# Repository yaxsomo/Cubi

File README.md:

### Description
Simple open source bluetooth controlled wheeled robot. Mechanical design, electronics and software designs available on this repo.
I used @Gregwar's Holo as a starting point.

The initial design is a cube like robot :

https://www.youtube.com/watch?v=2ZDV0_4vD0g

https://www.youtube.com/watch?v=TOusHRbKWQg

A second design was also made to play around cart-poling:

https://www.youtube.com/watch?v=Ubej95gH9Gs

TODO:

- Add Julien's O. designs and events

- Add Julien's A. and Jérémy's designs and event (cap science)

### Simulation
Some simulation stuff (simple kinematic control, inverted pendulum tests) is available in Python here :
https://bitbucket.org/RemiFabre/cubi/src/master/simulation/

0) Installation
You'll need Python (any version should work) and pygame
```
pip install pygame
```

1) Simple control of a wheeled robot (click around)
```
python main.py
```
https://www.youtube.com/watch?v=O8ZoUAvGYmE

2) Inverted pendulum (cart-pole) simulation
```
python cart_pole.py
```
https://www.youtube.com/watch?v=xhEcLnnj7fg

### How to make it work
You'll have to install the arm cross-compilation tools. On debian-like distributions,
you can get it with:

```
    sudo aptitude install build-essential git-core dfu-util openocd python \
        python-serial binutils-arm-none-eabi gcc-arm-none-eabi libstdc++-arm-none-eabi-newlib
```
If you're running an Ubuntu 14.04 or older, you might need to install the libstdc++-arm-none-eabi-newlib packet by hand. Download link :
http://ftp.de.debian.org/debian/pool/main/libs/libstdc++-arm-none-eabi/libstdc++-arm-none-eabi-newlib_4.8.3-9+4_all.deb

Command (if a conflict rises, you can add --force-overwrite to the following line):
```
	sudo dpkg -i libstdc++-arm-none-eabi-newlib_4.8.3-9+4_all.deb
```

Then go to Cubi/firmware/src and run :

```
bash ./prepare.sh
```

Then, go to the `firmware/` directory and edit the `Makefile` to set the appropriate
`BOARD` variable, targetting your servo.

You can then run:

```
make
```

Use an USB cable to connect your pc with the robot's board

```
make install
```
If you didn't follow this section to setup udev rules, you might need to ```sudo make install``` instead

http://static.leaflabs.com/pub/leaflabs/maple-docs/0.0.12/unix-toolchain.html#toolchain-udev

### Bluetooth
You can control the robot without the need of a cable. The most straight-forward way is to download the "Metabot" app from Google Play. Once on the app you can scan for devices, find your robot and pair it with your phone.

If you want to pair your PC with your robot, one method is as follows (Ubuntu).

Uninstall modemmanager (not needed but causes some issues)

```
    sudo apt-get purge modemmanager
```

Scan for bluetooth devices and save the adress (e.g. 98:D3:37:90:ED:D6) of your robot. For example, we use blueman-manager :

```
    sudo apt-get install blueman
    sudo blueman-manager
```

Assign a serial port to the connection. You can do that on the graphical interface of blueman-manager but doing it directly with rfcomm seems more robust :

```
    sudo rfcomm bind /dev/rfcomm0 98:D3:37:90:ED:D6
```

Now you can access the remote terminal on the robot with :

```
    cu -l /dev/rfcomm0
```

You might have permission access issues. Make sure you're in the dialout group or go bonkers :

```
    sudo chmod 777 /dev/rfcomm0 && cu -l /dev/rfcomm0
```

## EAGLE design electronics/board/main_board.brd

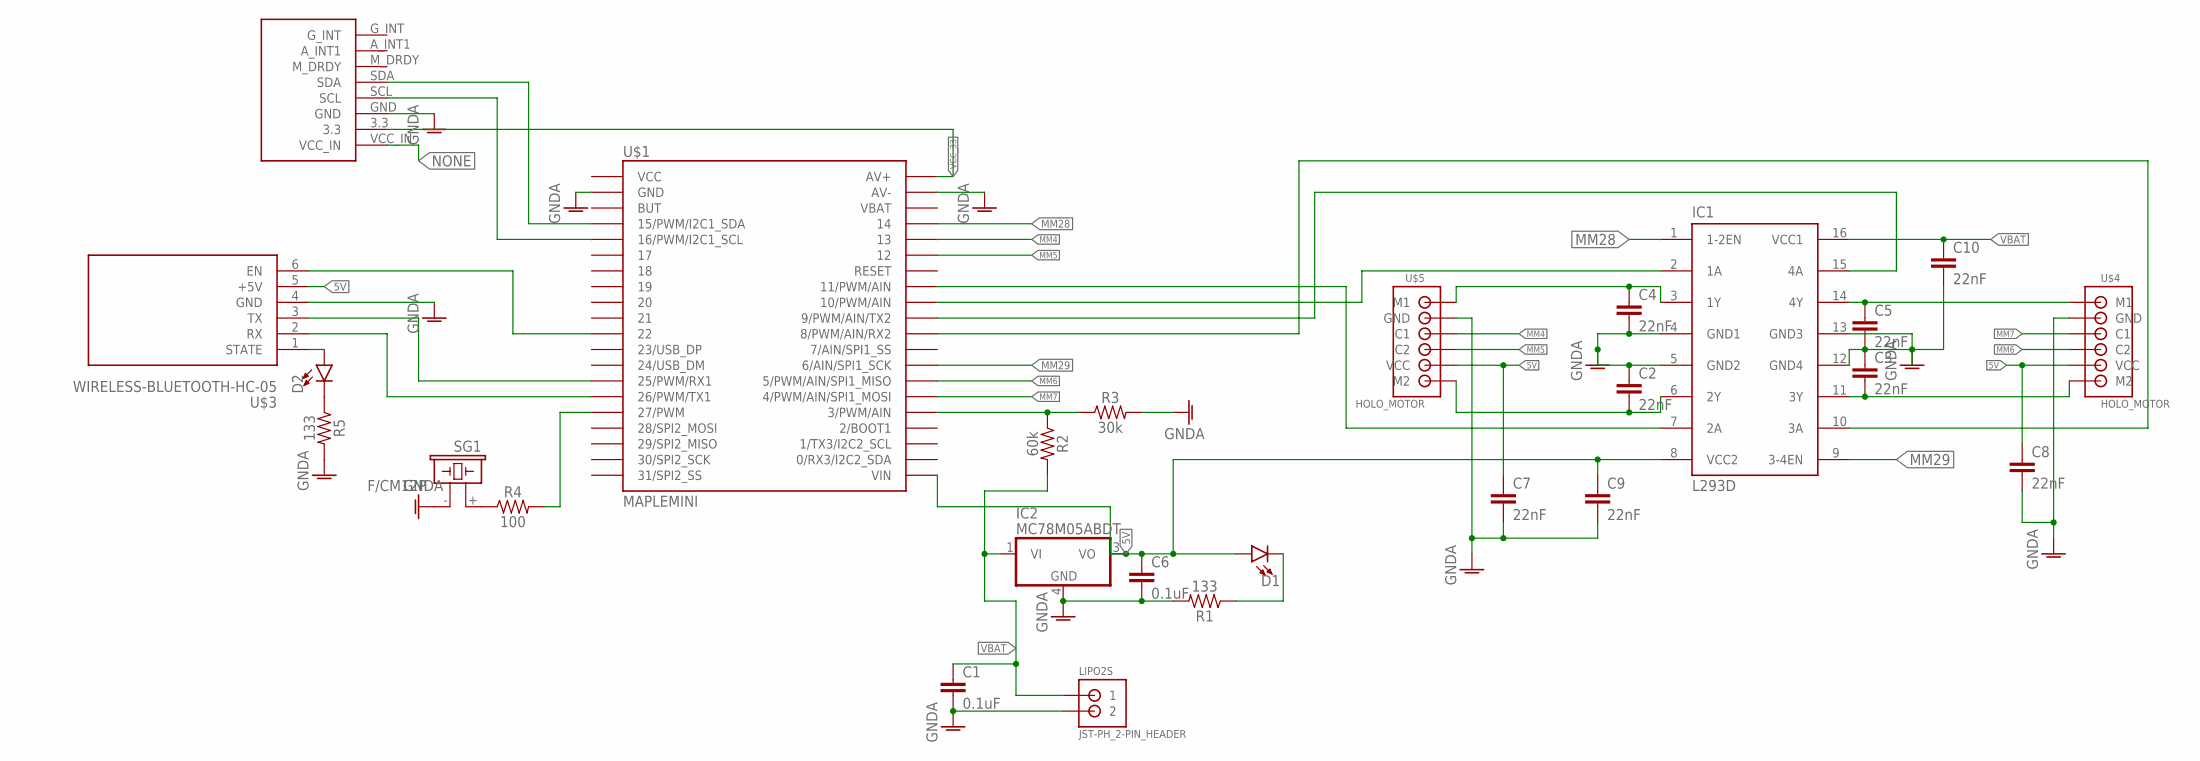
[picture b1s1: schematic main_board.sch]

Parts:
C1, C6: 0.1uF; 0603
C2, C3, C4, C5, C7, C8, C9, C10: 22nF; 0603
D1, D2: LED-FKIT-1206; FKIT-LED-1206
IC1: L293D; DIL16
IC2: MC78M05ABDT; DPACK_3
LIPO2S: JST-PH_2-PIN_HEADER; JST_B2B-PH_HEADER
R1, R5: 133; 0603
R2: 60k; 0603
R3: 30k; 0603
R4: 100; 0603
SG1: F/CM12P
U$1: MAPLEMINI; 20-DIP
U$3: WIRELESS-BLUETOOTH-HC-05
U$4, U$5: HOLO_MOTOR
U$6: GY-85

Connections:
5V: C6.1, C7.1, C8.1, C9.1, D1.A, IC1.8 (VCC2), IC2.3 (VO), U$1.21 (VIN), U$3.5 (+5V), U$4.5 (VCC), U$5.5 (VCC)
GNDA: C1.2, C2.1, C3.1, C4.2, C5.2, C6.2, C7.2, C8.2, C9.2, C10.2, IC1.4 (GND1), IC1.5 (GND2), IC1.12 (GND4), IC1.13 (GND3), IC2.4 (GND), LIPO2S.P2 (2), R1.2, R3.2, R5.2, SG1.- (2), U$1.2 (GND), U$1.39 (AV-), U$3.4 (GND), U$4.2 (GND), U$5.2 (GND), U$6.GND
MM4: U$1.36 (13), U$5.3 (C1)
MM5: U$1.35 (12), U$5.4 (C2)
MM6: U$1.27 (5/PWM/AIN/SPI1_MISO), U$4.4 (C2)
MM7: U$1.26 (4/PWM/AIN/SPI1_MOSI), U$4.3 (C1)
MM28: IC1.1 (1-2EN), U$1.37 (14)
MM29: IC1.9 (3-4EN), U$1.28 (6/AIN/SPI1_SCK)
unnamed: D1.C, R1.1
unnamed: R4.2, U$1.16 (27/PWM)
unnamed: IC1.10 (3A), U$1.30 (8/PWM/AIN/RX2)
unnamed: U$1.15 (26/PWM/TX1), U$3.2 (RX)
unnamed: U$1.14 (25/PWM/RX1), U$3.3 (TX)
unnamed: U$1.5 (16/PWM/I2C1_SCL), U$6.SCL
unnamed: C5.1, IC1.14 (4Y), U$4.1 (M1)
unnamed: U$1.11 (22), U$3.6 (EN)
unnamed: R2.1, R3.1, U$1.25 (3/PWM/AIN)
unnamed: IC1.7 (2A), U$1.33 (11/PWM/AIN)
unnamed: IC1.2 (1A), U$1.32 (10/PWM/AIN)
unnamed: IC1.15 (4A), U$1.31 (9/PWM/AIN/TX2)
unnamed: U$1.4 (15/PWM/I2C1_SDA), U$6.SDA
unnamed: R4.1, SG1.+ (1)
unnamed: C4.1, IC1.3 (1Y), U$5.1 (M1)
unnamed: C3.2, IC1.11 (3Y), U$4.6 (M2)
unnamed: C2.2, IC1.6 (2Y), U$5.6 (M2)
unnamed: D2.A, U$3.1 (STATE)
unnamed: D2.C, R5.1
NONE: U$6.VCC_IN
VBAT: C1.1, C10.1, IC1.16 (VCC1), IC2.1 (VI), LIPO2S.P1 (1), R2.2
VCC_33: U$1.40 (AV+), U$6.3.3

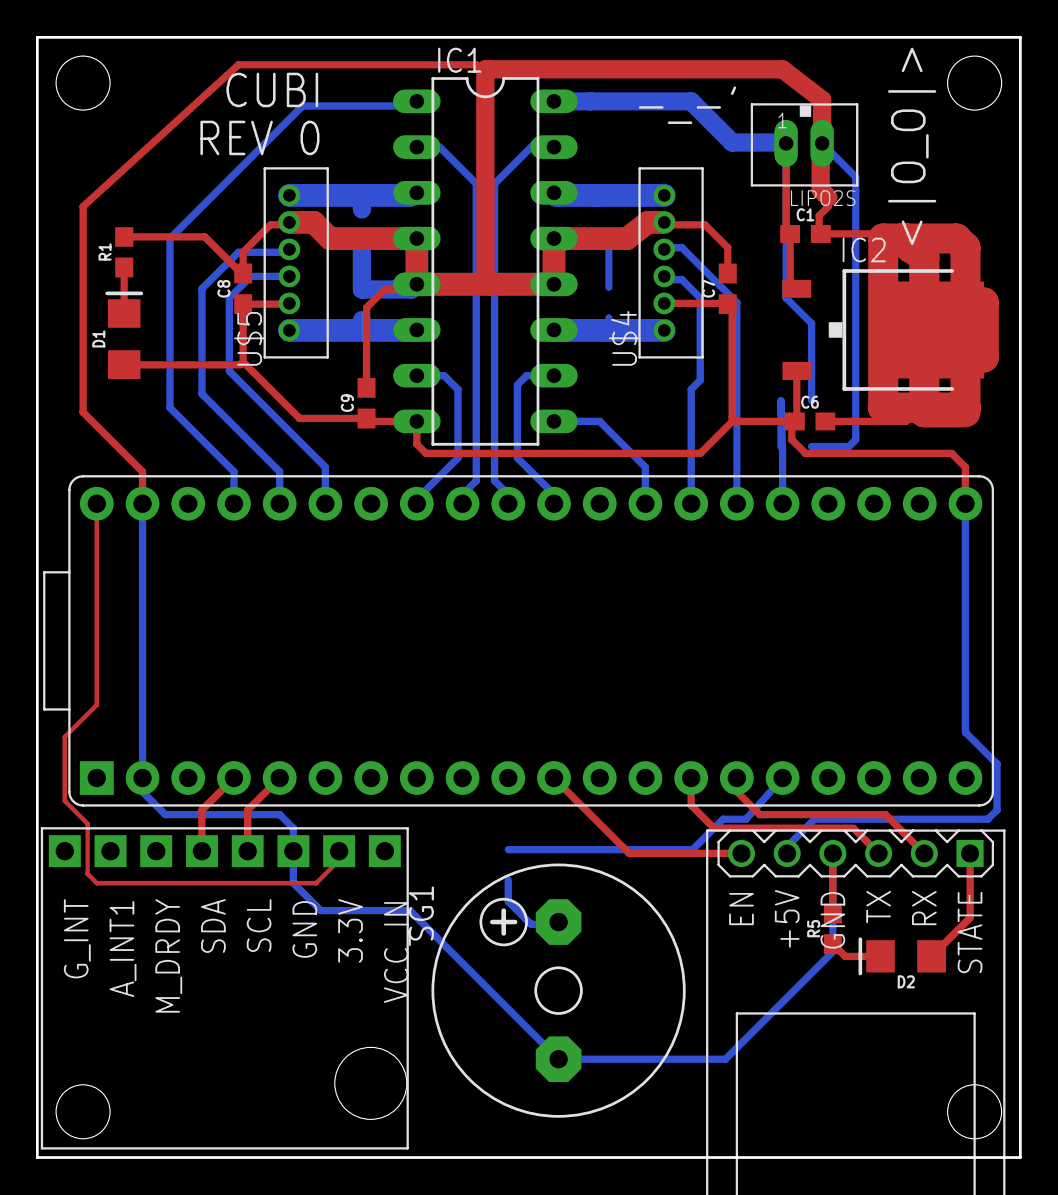
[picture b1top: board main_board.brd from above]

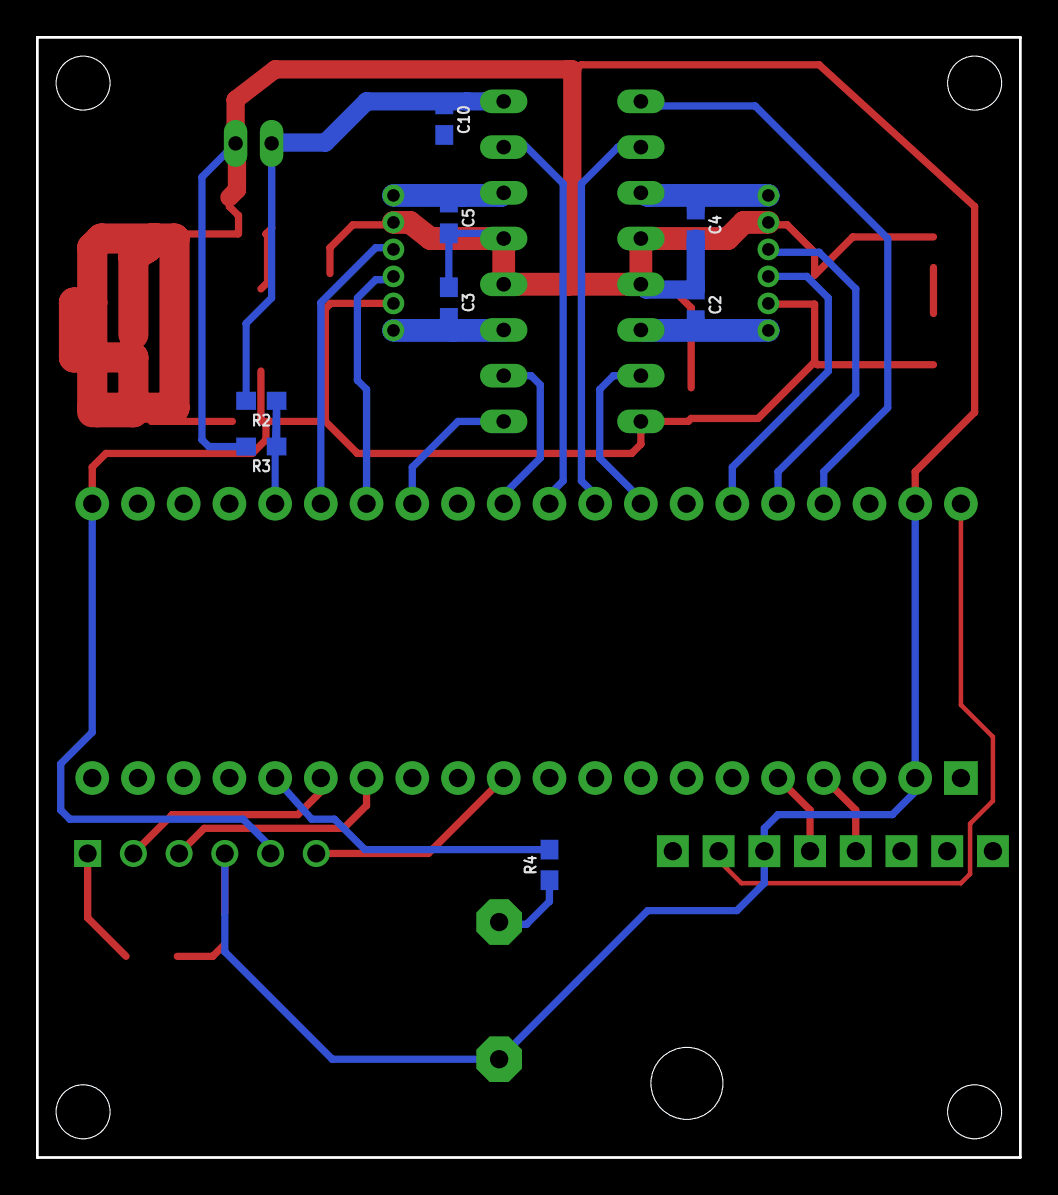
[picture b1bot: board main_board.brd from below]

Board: 2 copper layers, 54.6 x 62.2 mm, 26 parts (8 on the bottom side), 29 nets.

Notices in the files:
parts and their libraries:
SparkFun-Capacitors: Licensing: Creative Commons ShareAlike 4.0 International - https://creativecommons.org/licenses/by-sa/4.0
diy-modules: Released under the Creative Commons Attribution 4.0 International License: http://creativecommons.org/licenses/by/4.0
